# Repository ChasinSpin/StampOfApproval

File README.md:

# Stamp Of Approval

* [Introduction](#introduction)
* [Features](#features)
* [Purpose](#purpose)
* [Design Goals](#design-goals)
* [Buttons](#buttons)
* [Timing Pulse Mode](#timing-pulse-mode)
* [Flasher](#flasher)
* [LED Driver](#led-driver)
* [Power](#power)
* [Acquisition Requirements](#acquisition-requirements)
* [Leap Seconds](#leap-seconds)
* [TFT Time Display Accuracy](#tft-time-display-accuracy)
* [Poor GPS Signal](#poor-GPS-Signal)
* [Forcing GPS Cold Restart](#forcing-gps-cold-restart)
* [Analyzing Timing](#analyzing-timing)
* [States](#atates)
* [WWV Testing](#wwv-testing)
* [Assembled Version](#assembled-version)
* [BOM Bill Of Materials](#bom-bill-of-materials)
* [Construction](#construction)
* [Installing](#installing)
* [Reset to factory defaults](#reset-to-factory-defaults)
* [Specifications](#specifications)
* [Developer Notes](#developer-notes)
* [Release Notes](#release-notes)

## Introduction

Stamp Of Approval (SOA) is a highly accurate timing device to verify Occultation Transit Eclipse (OTE) timing.  Accurate and repeatable time is critical for OTE events. SOA is used to test the timestamping accuracy on frames from cameras and occultation flashers through to the OTE application to provide a level of confidence in the timing for the devices and processes involved. It can also double up as a basic programmable flasher device.

SOA consists of a microcontroller with a display, a GPS receiver with Pulse Per Second (PPS) output, and an LED flasher. To verify timing, a flash on the LED is generated, which should be fed to your acquisition system and timed with software like [pymovie](https://github.com/bob-anderson-ok/pymovie) or [py-ote](https://github.com/bob-anderson-ok/py-ote).

Note:

	Using flasher-type devices for occultations adds extra 
	complexity and possibility for user error in the acquisition/analysis
	process.  It also often calls into question the observer's timing 
	which can be dependent on the flasher device/code used, who 
	built it etc.
		
	A better solution is to use Astrid as a complete acquisition 
	system (which also includes the computer/camera/frame timing/
	plate solving/prepoint).

## Features

* **240x135 Color TFT Display + buttons**
* **User Error proof**
	* *No information is provided if the GPS signal is not adequate, green = OK, red = BAD e.g. traffic light*
* **Validates your complete timing**
	* *e.g. flashers, VTI, [Astrid](https://github.com/ChasinSpin/astrid)), your processes and analysis*
* **Highly accurate timing**
	* *at 30fps result is accurate to 0.0001s or less after analysis in Py-OTE*
* **Hardware Gated Timing**
	* *The LED pulse comes directly from the GPS and is not dependent on Input Capture Registers or Interrupts in software.  This results in close to zero hardware delay between the GPS issuing the timing pulse and the LED flashing - 53 nanoseconds (other Flashers issue the LED pulse themselves from software, resulting in delays and possible race/non-deterministic behavior).*
* **10-second pulse alignment aligned on 00, 10, 20, 30, 40, 50 seconds UTC**
	* *1-second pulses are difficult to check time against by other means (a clock can be wrong), however, an error of 10 seconds is very easy to spot*
* **Leap seconds dealt with correctly**
	* *No leap seconds = no time output... simple*
* **Doubles up as a basic regular flasher**
* **Accurate Latitude / Longitude / Altitude**
* **Monitors and notifies for signal issues**
	* *Number of Satellites, Fix, Dilution of Precision, PPS Drops*
* **Analog Adjustable LED Brightness**
	* *No PWM delays*
	* *No need to program brightness*	 
	* *Full range*
* **Constant Current and Regulated LED Driver**
	* *Flatter pulses for more accurate timing*
	* *Immunity to brightness drops due to CPU processing which impacts timing*
* **External antenna for better GPS signal**
* **Open source**
* **Specifications sheet with accuracy detailed**
* **Platform agnostic, Mac/Windows/Linux… all good**

## Purpose

SOA is intended to verify timing from start to finish, i.e., the time of a calculated "Flash" in PyOTE or other D/R timing analysis software is the end goal, and it's the result should be evaluated. If the time is incorrect, then the cause needs to be determined.

However, SOA only verifies the time at the point in time the test is run.  It is quite possible (and likely in some circumstances) that poorly written software/firmware or clock synchronization in your acquisition system or flasher may result in a system that appears to behave well at some points in time and provides incorrect timing at other points in time.

## Design Goals

SOA is designed to keep the output as close to the raw GPS output as possible to reduce the risk of software issues impacting timing.  Additionally, the LED flasher signal is taken directly from the GPS receiver so that there is no impact on timing from any of the usual processing delays inherent to microcontrollers.

SOA does not allow the user to think they have good timing when they do not, it's designed according to the traffic light principle, such that if "Status" is Green, then you can have confidence in the timing.  If it is any other color (typically Red), then you should not rely on the timing and should improve your GPS Signal.

Typical code optimization methods, i.e., anything that makes the code more difficult to understand/analyze by another party, have been avoided.  The code is written in Python (specifically Circuit Python) for a larger audience.  Due to the above approach, it's possible to use Python without compromising the timing.

## Buttons

SOA has 2 modes, and to switch between modes, you press the <D1> button:

* Monitoring: This is the default and will be used until a good fix is acquired; the LED flasher flashes every second. This should not be used to check your timing.
* Timing Pulse: The LED-flasher flashes on a 10-second mark, e.g., 10:32:20 UTC. 

The <D2> button is used to toggle between displaying satellite signal status and position/altitude.

## Timing Pulse Mode

Timing pulse mode is used to verify your timing. At least a blank 4-second period is provided on either side of the flash, and the time of the flash is provided. Your camera/acquisition/OTE Software captures and analyzes this flash, and the timing accuracy of your system can be determined. The appearance time of the flash in your OTE Software should match the time provided by SOA. The duration of the pulse is 6 seconds.

If you are using a flasher, too, as part of your acquisition system, you will need to align your time in your OTE Software using those flashes first, prior to determining the time on your SOA LED-flasher pulse.

Button <D1> is used to initiate the Timing Pulse blanking period and subsequently pressed to initiate the pulse. Button <D2> is used to toggle the location display.

## Flasher

It's possible to operate SOA as a basic programmable and highly accurate flasher, although that is not the design goal. There are better solutions than flashers. For example, [Astrid](https://github.com/ChasinSpin/astrid) would be a preferred solution, and if you absolutely have to use a flasher, then IOTA-GFT (coming soon) is a well-designed flasher too.

Flasher behavior is kept very simple in SOA and requires a Good Signal for the flash to occur.  It's bare bones; all it does is flash the LED at the times you choose, as detailed below.  There's no extra fluff like countdowns etc.  However, it does that with very high accuracy as it uses the same hardware gating of the GPS signal and is more accurate than other flasher solutions.

It is suggested that you issue multiple flashes before and after the event just in case one of the flashes is not successful due to poor signal quality. SOA (for reasons of complexity reduction) does not maintain its own timebase in the event that the signal is lost.

To use SOA as a flasher, create a plain text file on your PC called: flasher.txt

Inside, put the UTC times you wish the flashes to occur, one per line, and in HH:MM:SS format aligned on 10-second UTC boundaries (00, 10, 20, 30, 40, 50 seconds), for example:

	05:08:10
	05:09:10
	05:10:10
	05:12:00
	05:13:00
	05:14:00
	
**IMPORTANT: Be aware that each flash is 6 seconds long, remember to factor that in such that your observation isn't impacted by the flash.**

Connect SOA via USB to your computer, and copy the flasher.txt into the CIRCUITPY drive.  

SOA will restart shortly and read the flasher.txt file.  If this read is successful and the file is correctly formatted, then it will enter "Flasher" mode and display the first 4 times to indicate the flasher.txt file has been successfully read.  If the file is empty or contains errors, then an error message will be displayed instead.

In flasher mode, the LED will flash at the times specified with 6-second pulses aligned with the LED coming on at the time of the PPS pulse from the GPS.

To return to regular operation (non-flasher), then remove the flasher.txt file.

If you need to tune the brightness of the LED to avoid saturation with your camera, then press button <D1> to enter 1-second pulse mode (this pulses for 0.9s on and 0.1s off). You will need to press <D1> again to return to flasher mode before the event.

The <D2> button will toggle between the signal quality display and Latitude/Longitude/Altitude display.

Unlike [Astrid](https://github.com/ChasinSpin/astrid), SOA does not maintain an audit trail for its flasher functionality, it is advisable to monitor SOA visually during acquisition.

## Power

SOA must be powered via the microcontroller's USB-C port, not the JST battery port or the GPS USB port.

To power via the USB-C port, either connect to a computer or power via a USB PowerBank. Any USB cable to the computer needs to be both power and data-capable. 

## LED Driver

The LED driver design in SOA uses an adjustable brightness, regulated analog-driven constant current design that does not overdrive the LED, use voltage drive, or PWM.

This has some advantages over regular designs, which leads to more accurate timing in your OTE software:

* No variable PWM mid-cycle delays
* No dropouts in brightness due to processor activity/load
* Flatter start to the pulse 

## Acquisition Requirements

It's critical that the LED flasher signal on your camera/acquisition system is not saturated. If it is, then the signal cannot be interpolated to get accurate timing by the OTE Software, as information has been lost due to clipping of the signal (saturation). However, to get the maximum signal-to-noise ratio and, therefore, accuracy in time, you should adjust the LED flasher output so that it fills most of the camera's range.

It's also important that there is no artificial light ingress into the optical train to your camera.  For example, most electrical items that emit light will either be running at 60/50Hz or be Pulse Width Modulated (PWM) which means that the light source is switching on and off fast (beyond the ability of your eye to register), however, this can result in artifacts in camera frames, where intensities are not correct, leading to timing problems when interpolated.

Generally, it is advised to insert the LED into the light path of the telescope or via a light-tight tube to the camera if on a bench. A lens to bring an image to focus can also be used; however, because the light is focused, there likely will be saturation.

## Leap Seconds

SOA refuses to provide a time when it's not aware of the Leap Seconds downloaded from the GPS Almanac.  This awareness can come from an Alamanc download (every 12.5 minutes via GPS) or from a previous almanac download stored via battery backup and non-volatile memory on the GPS receiver.

As SOA won't provide a time without knowing the leap seconds, there is ordinarily no requirement to be concerned with Leap Seconds. The exception to this is if there has been a leap second change since you last used SOA and you are within 12.5 minutes of getting that initial time. In this situation, the time may be offset. Such cases are extremely rare, but you can check the current number of leap seconds or wait 12.5 minutes for the Alamanac update.

## TFT Time Display Accuracy

VERY IMPORTANT: To test timing accurately, you MUST use the LED flasher, not the TFT Time Display.

SOA is only accurate for the LED flasher, which aligns with the start of a second.  The TFT Display on SOA (which displays the time) always updates after the start of the second, but before the next and is typically late by about 270ms.  Therefore it shouldn't be used for timing other than approximately to within 0.3s.  It has been purposely designed this way so that the code associated is minimal and thus provides minimally processed output from the GPS.

## Poor GPS Signal

Possible reasons are:

* Antenna upside down (black part not pointing to the sky)
* Usage inside (the top floor of a house may work depending on construction, but outside is better)
* Obstructed view of the sky (trees, buildings, etc.), GPS requires a clear 360-degree view of the sky
* Placed on metal. Although the antennas are magnetic, the metal often creates a ground plane and can make reception unpredictable; avoid metal other than a nail or a bolt
* Placed on the ground. Ground is an unpredictable ground plane; often, grass/dirt interferes with the signal, and a concrete slab may not, experience varies, avoid.
* Attached to a telescope.  Telescopes move and are often metal both of which will interfere with signal reception
* Poor cable connection.  Ensure the antenna cable is fully screwed in and the antenna hasn't disconnected from the GPS receiver
* Broken antenna

## Forcing GPS Cold Restart

A cold restart is when the Almanac/Time/Satellite Ephemeris and all State Information are deleted from the GPS forcing it to be downloaded again.  A GPS cold started will take longer to provide position and time.

To force SOA to cold start place an empty file called coldstart.txt on the CIRCUITPY drive when connected to a computer, then eject the drive from the computer. SOA will then auto restart, send the cold start instruction to the GPS and delete the coldstart.txt file so that on the next boot, the GPS will return to normal warm start behavior.

## Analyzing Timing

Pymovie/Py-OTE is used as an example here. If you are using other OTE software, please provide information on how to use it so that it can be added to this documentation.

The device you are testing (Device Under Test = DUT) can either be a Flasher or an acquisition system that times frames directly or by computer.

### DUT = Flasher

With a DUT=Flasher device, you ordinarily correct your timing via the Calc Flash, etc. method in Py-OTE using a Flash Aperture. This means you bracket your recording with at least a flash on either side. As you are doing this already, it is assumed that you know how to do this.

However, the SOA flash should be in the middle, so you want three flashes:

	DUTFlash -> SOA Flash -> DUTFlash.

### DUT = Other (e.g., [Astrid](https://github.com/ChasinSpin/astrid), IOTA-VTI, etc.)

These devices don't need to have their timing corrected (although IOTA-VTI needs to have OCR applied to its timing; again, you'll know how to do this).

Only one flash is required, the SOA Flash.

### Analyzing the SOA Flash

To time the SOA Flash, you need to time ONLY the rising edge of the SOA Flash (the trailing edge will always be less accurate due to the physics of LEDs).

To do this, first, create a Flash Aperture in Pymovie and analyze the video as normal. Then, in Py-OTE, trim the waveform so only the rising (R edge or Reappearance edge) is left. (If the D edge or anything else is present, it won't work.)

Then mark the R edge as normal, and click on Find Event to get the timing of the R edge.

It's important to ensure that you have at least 12 or more frames before and after the rising edge so that Py-OTE can determine an accurate answer.

## States

SOA has the following states, and follows the traffic light principle, Red, Amber, Green with the addition of a magenta for unknown:

| State/Msg | Description | Reports | Color |
| --------- | ----------- | ------- | ----- |
| No GPS | No communication with GPS | - | Magenta |
| No Signal | GPS is running, but no satellites acquired yet | - | Red |
| Acquiring (no PPS) | GPS has at least one satellite but not enough to provide PPS  | #satellites | Red |
| Waiting For Leap Seconds | GPS has PPS but is waiting for leap seconds via the Almanac | #satellites | Red|
| Poor Fix | GPS has PPS and time, but fails quality checks (HDOP, VDOP, #Satellites, 3D Fix) | UTC, HDOP, VDOP, Satellites and PPS | Red |
| Good Fix | GPS has PPS and time and passes quality checks (HDOP, VDOP, #Satellites, 3D Fix) | UTC, HDOP, VDOP, Satellites and PPS | Green |
| Timing Pulse | Displays the UTC time the 6-second timing pulse was started (the LED came on) | Time of Pulse | Green |

## WWV Testing

SOA has had the edge sense of the PPS pulse checked by extending the pulse duration to 600ms and comparing by audio against the WWV radio signal.  Note that this isn't to confirm a precise time.  However, it does confirm that the rising edge of the pulse matches the time markers on WWV and that the GPS isn't providing the sync on the falling edge (as the UBlox documentation in regard to this is ambiguous).  It also confirms the time provided as UTC is accurate to the second.

## Assembled Version

### Includes

* Stamp Of Authority:
	* Display
	* GPS Receiver
	* Case
* GPS Active Antenna
* LED on magnetic mount (with 1.5m wire)

### Purchase Required

USB-C Male to USB-A Male cable

**OR**

USB-C Male to USB-C Male 
cable

*cable must be power and data capable*

## BOM Bill Of Materials

| Quantity | Part | Value | Tolerance | Package | Description | Notes |
| -------- | ---- | ----- | --------- | -------- | ----------- | ----- |
| 1	 | R1 | 10 | 1% | 0603 | Resistor | |
| 1	 | R3 | 33K | 1% | 0603 | Resistor | |
| 1	 | R2 | 1K | 5% | 0603 | Resistor | |
| 1	 | R5 | 10K | 5% | 0603 | Resistor | |
| 1 | RP1 | 1K Log | - | Pot | PTV09A-4030F-A102 1K Log Potentiometer | |
| 1 | C2 | 0.1uF | 20 % X5R/X7R | 0603 | Capacitor | |
| 1 | C1 | 0.47uF | 20 % X5R/X7R | 0603 | Capacitor | |
| 1 | LED1 | WP7113SURDK | - | T1-3/4 5mm | LED | Do not substitute |
| 2 | Q1, Q2 | MMBT3904LT1G | - | SOT23 | Transistor | Do not substitute |
| 1 | U1 | MIC5203-3.3YM5 | - | SOT23-5 | 3.3V Regulator | |
| 1 | U2 | MCP6486RT-E/OT | - | SOT23-5 | Rail to rail Op-amp | Do not substitute. Make sure it's the RT version, regular version has supply rails switched |
| 1 | - | PPPC121LFBN-RC | - | - | 12 Pin 0.1 Female Header | |
| 1 | - | PPPC161LFBN-RC | - | - | 16 Pin 0.1 Female Header | |
| 1 | MS1 | 5345 | - | Feather | Adafruit ESP32-S2 TFT Reverse | Do not substitute |
| 1 | MODULE1 | GT-U7 | - | GT-U7 | GT-U7 Ublox 6M Compatible GPS Receiver | Do not substitute |
| 1 | Antenna | BFN00457 | - | - | Bingu Waterproof Active GPS Navigation Antenna Adhesive Mount SMA Male GPS Antenna with 15cm 6inch U.FL IPX IPEX to SMA Female RG178 Coaxial Pigtail Cable for GPS Module Receiver Tracking | |
| 1 | CASE | - | - | - | Case & Buttons | |
| * TBD * | | | | | Nuts | |
| * TBD * | | | | | Bolts | |
| 2 | - | - | - | - | Small Zip Tie max 3mm width | |
| 1 | PCB | - | - | - | Main PCB | |
| 1 | PCB | - | - | - | LED Carrier PCB | |
| 1 | - | - | - | - | 1.5m Double Conductor Wire | |
| 1 | R4 | DNP | DNP | 0603 | Resistor | Do not populate |
| 1 | D1 | DNP | DNP | Diode | CUS08F30,H3F | Do not populate |

## Construction

SOA is provided completely assembled. Construction details coming soon.

## Installing

First installation:

* Connect SOA to computer via USB cable (data and power capable)
* Fast double-tap the reset button, then tap again 1 second later, SOA will enter bootloader mode and provide a Green/Blue/Orange Background
* Place the file: 
`circuitpython/adafruit-circuitpython-adafruit_feather_esp32s2_reverse_tft-en_US-8.2.9.uf2`
in the FTHRS2BOOT drive on the computer and wait for SOA to reboot
* Download: [SOA V1.0.0 Zip File](https://github.com/ChasinSpin/StampOfApproval/raw/main/soa_1_0_0.zip), unzip the file and place all the files and folders found within the "soa" folder into the "CIRCUITPY" drive that appears on the computer and wait for SOA to start.  Note: Keep the folder names and their contents intact.  It's important to copy what's in the soa folder, not the soa folder itself onto the drive.

For subsequent upgrades, you can start from the last item on the above list as Circuit Python is now already installed.

Note: More recent Macs may get a -36 error when copying files into SOA; this error can be ignored.

## Reset to factory defaults

Reference: [Factory Reset](https://learn.adafruit.com/esp32-s2-reverse-tft-feather/factory-reset)

To reset, power up with a USB cable connected to a computer, fast double-tap the reset button, and tap again a fraction of a second later (while purple). The Feather TFT screen should be displayed with a Green/Blue/Orange background.

Drag and drop 
`other/adafruit_feather_esp32s2_reversetft_factory_reset.uf2` onto FTHRS2BOOT drive and wait for reboot.

## Specifications

| Feature | Measurement |
| ------- | ----------- |
| Power Supply | USB-C Cable (power and data capable) - 5V |
| Power Usage | 100-170mA |
| GPS | GT-U7 Module (UBlox NEO-6M) |
| Display | 240x135 Color TFT |
| Buttons | 3 + Reset |
| Monitor Mode LED Pulse | 100ms on, 900ms off when acquired, rising edge on the second |
| Timing Mode LED Pulse | 6s on, 4s off when acquired, rising edge on a UTC 10-second boundary |
| Programming Language | Circuit Python V8 |
| LED Driver | Analog with Constant Current Adjustable Driver |
| GPS PPS to LED output delay (op-amp) | < 53ns |
| GPS Accuracy | 2.35ns over 6 hours with sampling deviation of 6.7ns |
| LED Current Range | 33.4uA - 9.5mA |
| Pulse brightness decay @ 9.5mA LED Current over 1 second | 0.227% (~0.0001s timing error in Py-OTE @ 33fps) |
| Pulse brightness decay @ 1.8mA LED Current over 1 second | 0.073% (~0.0000s timing error in Py_OTE @ 33fps)|

## Developer Notes

[https://github.com/todbot/circuitpython-tricks?tab=readme-ov-file](https://github.com/todbot/circuitpython-tricks?tab=readme-ov-file)

## Release Notes

### Version 1.0.0

Initial version

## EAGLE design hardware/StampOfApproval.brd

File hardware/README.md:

## Version 0.9a
	
* Initial

## Future Ideas

## Testing

1.

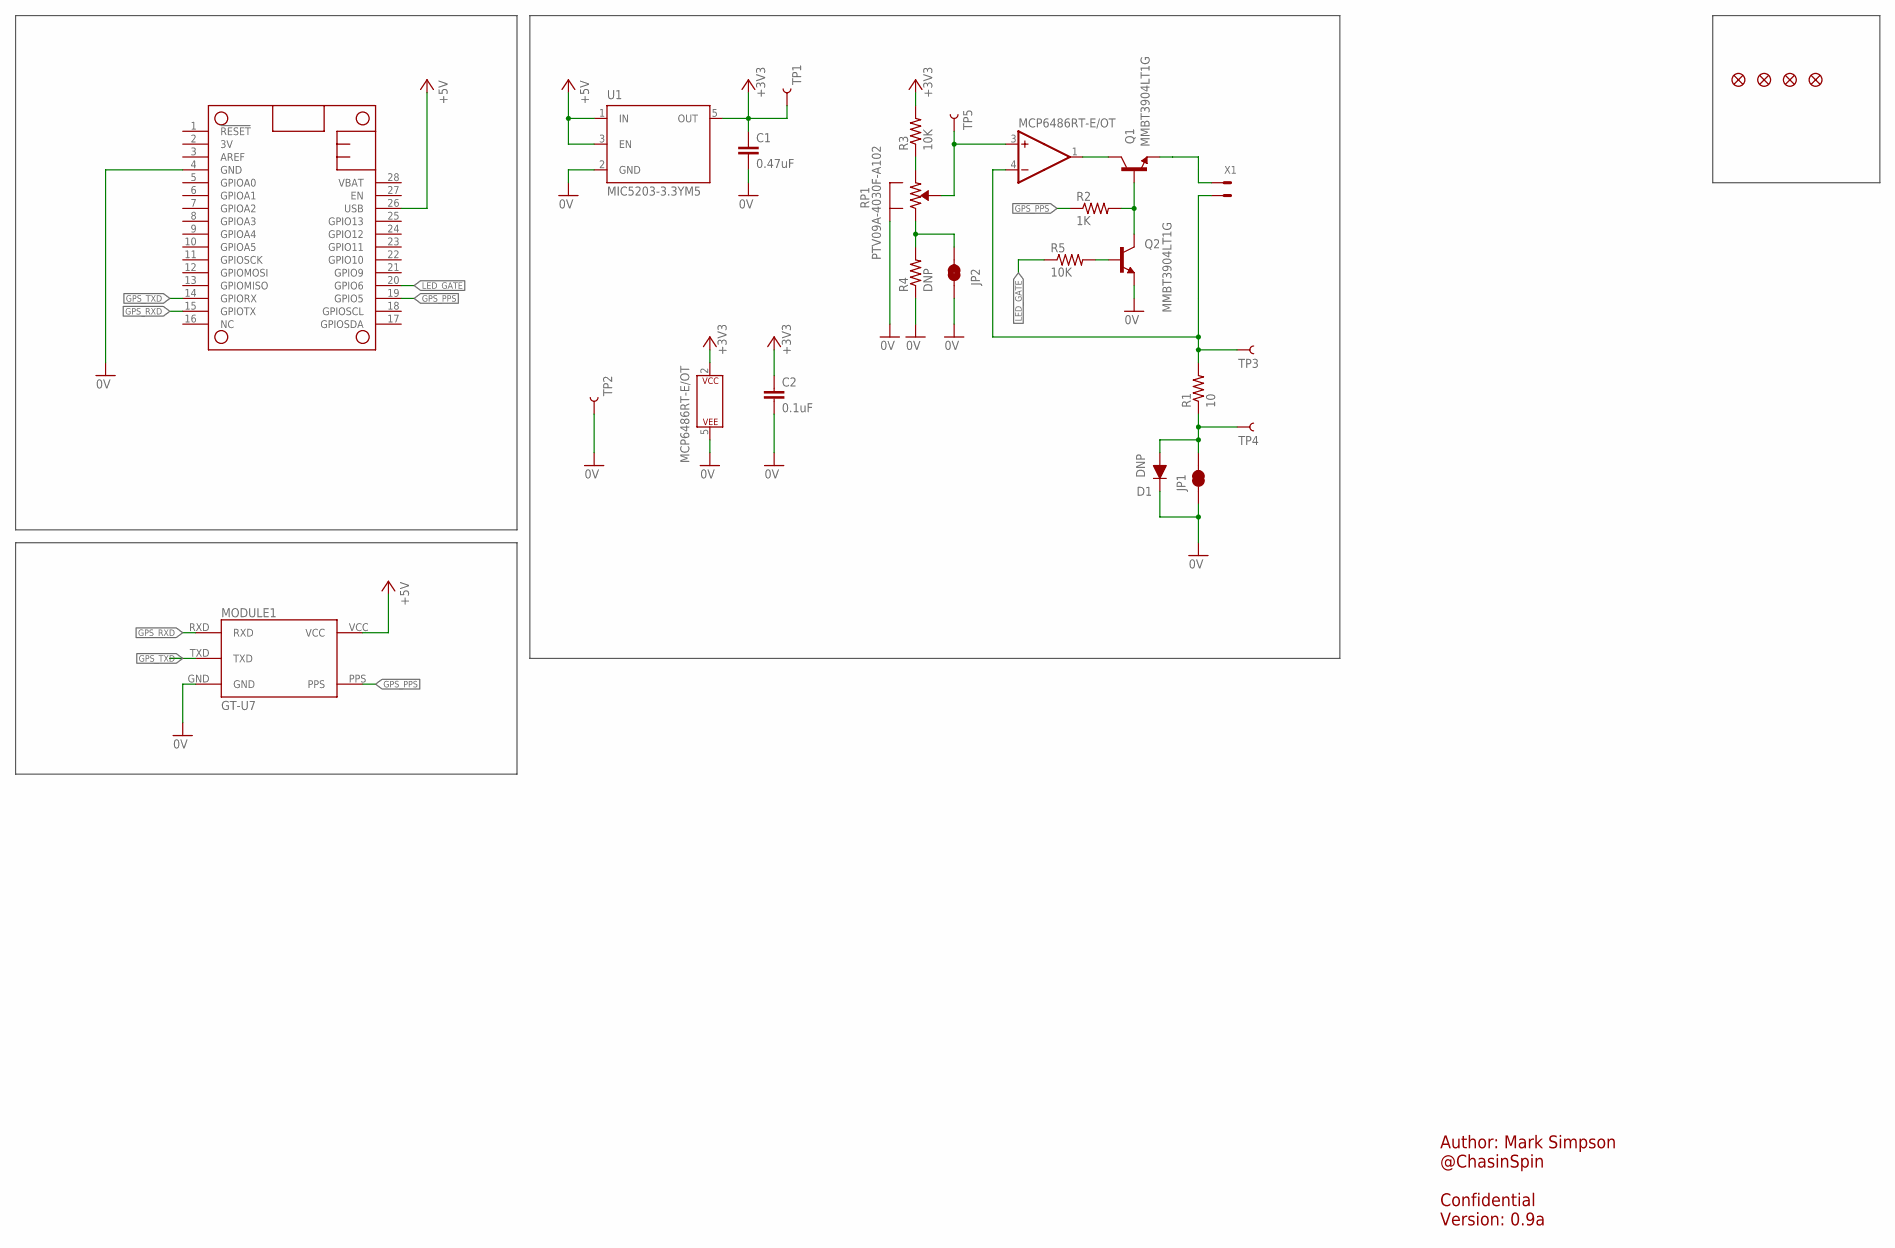
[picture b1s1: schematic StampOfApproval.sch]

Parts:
C1: 0.47uF; C0603K
C2: 0.1uF; C0603K
D1: DNP; CUS08F30
FD1, FD2, FD3, FD4: FIDUCIALUFIDUCIAL; FIDUCIAL-MICRO
JP1, JP2: JUMPER-SMT_2_NC_TRACE; SMT-JUMPER_2_NC_TRACE_SILK-WIDEPOWER
MODULE1: GT-U7
MS1: FEATHERWING_NODIM; FEATHERWING_DIM
Q1, Q2: MMBT3904LT1G; SOT23-BEC
R1: 10; R0603
R2: 1K; R0603
R3, R5: 10K; R0603
R4: DNP; R0603
RP1: PTV09A-4030F-A102; PTV09A-4
TP1, TP2, TP3, TP4, TP5: TEST-POINT3; PAD.03X.03
U1: MIC5203-3.3YM5; SOT23-5
U2: MCP6486RT-E/OT; SOT23-5
X1: SOLDER_CONTACTS

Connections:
0V: C1.2, C2.2, D1.K, JP1.1, JP2.1, MODULE1.GND, MS1.4 (GND), Q2.E, R4.1, RP1.SHIELD1 (SHIELD), RP1.SHIELD2 (SHIELD), TP2.P$1, U1.2 (GND), U2.5 (P$V-)
+3V3: C1.1, C2.1, R3.2, TP1.P$1, U1.5 (OUT), U2.2 (P$V+)
+5V: MODULE1.VCC, MS1.26 (USB), U1.1 (IN), U1.3 (EN)
GPS_PPS: MODULE1.PPS, MS1.19 (GPIO5), R2.1
GPS_RXD: MODULE1.RXD, MS1.15 (GPIOTX)
GPS_TXD: MODULE1.TXD, MS1.14 (GPIORX)
LED_GATE: MS1.20 (GPIO6), R5.1
unnamed: Q1.C, U2.1 (OUT)
unnamed: Q1.E, X1.1
unnamed: R1.2, TP3.P$1, U2.4 (-IN), X1.2
unnamed: D1.A, JP1.2, R1.1, TP4.P$1
unnamed: RP1.2 (WIPER), TP5.P$1, U2.3 (+IN)
unnamed: R3.1, RP1.3 (CCW)
unnamed: JP2.2, R4.2, RP1.1 (CW)
unnamed: Q1.B, Q2.C, R2.2
unnamed: Q2.B, R5.2

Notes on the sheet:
Author: Mark Simpson @ChasinSpin Confidential Version: 0.9a

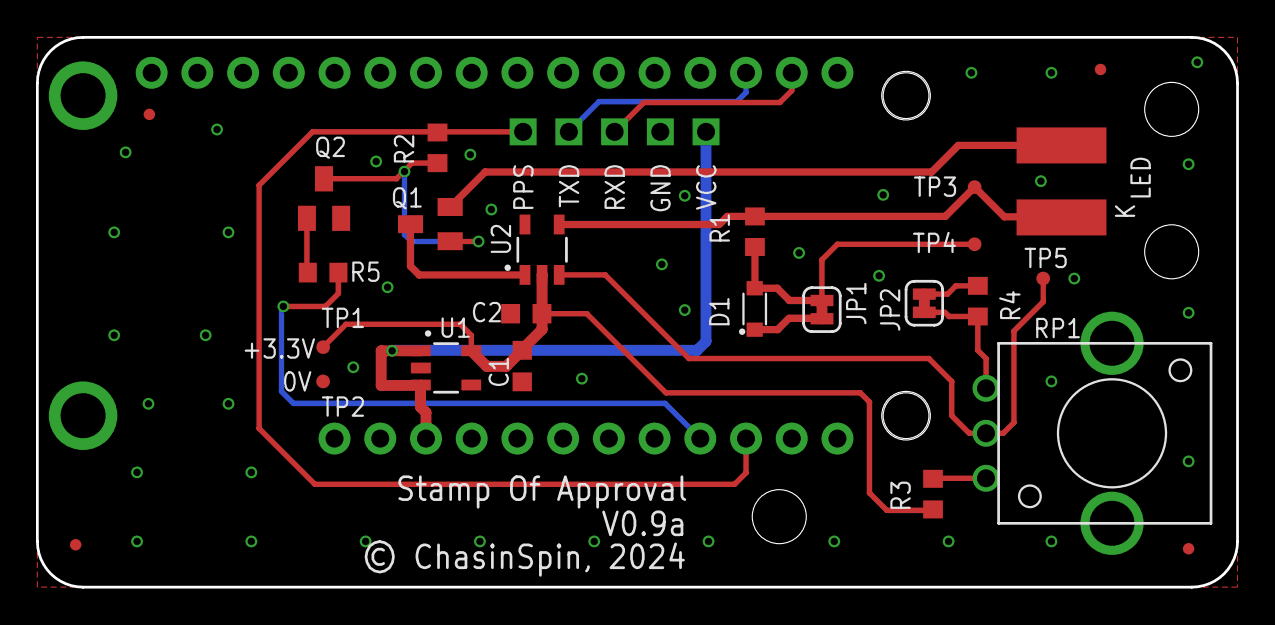
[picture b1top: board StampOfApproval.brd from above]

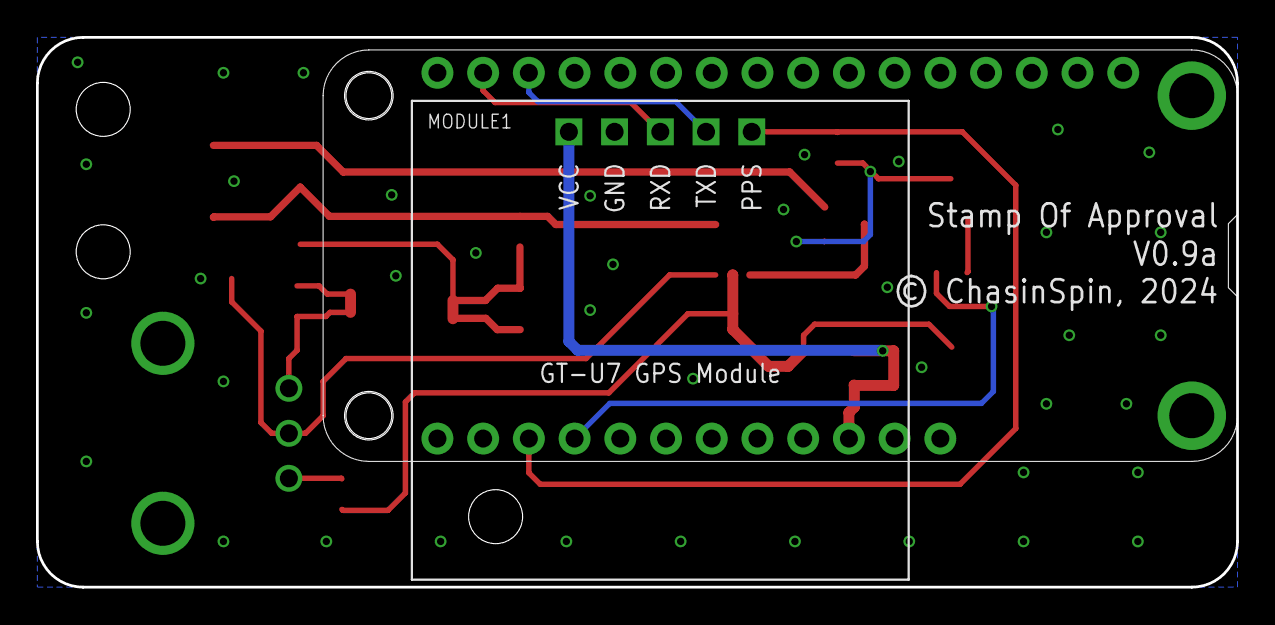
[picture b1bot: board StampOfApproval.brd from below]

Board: 2 copper layers, 66.7 x 30.5 mm, 27 parts (2 on the bottom side), 16 nets.

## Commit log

2024-03-13 Initial Version
2024-03-13 Deleting flasher.txt
2024-03-13 Updated PCB labels and took "Cream" off LED pads for stencil.
2024-03-14 Adding distribution zip
2024-03-14 Updateing makedist and README
2024-03-28 Adding Case

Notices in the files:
hardware/StampOfApproval.brd:
© ChasinSpin, 2024
